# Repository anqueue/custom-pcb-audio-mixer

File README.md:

# Custom PCB Audio Mixer

Deej is an open source project that allows an Arduino to control the volume of applications (https://github.com/omriharel/deej). I wanted to make my own mixer for this, however I don't have a 3d printer. Instead I opted for sandwiching two PCBs to house the electronics and connect the sliders to the Arduino.

The PCBs, Arduino Pro Micros, Poteniometers, soldering iron, bolts, and nuts, costed around $50-60.

I opted for Pro Micros as they have a USB-C connector, which is far more sturdy than the Micro USB on the traditional Arduino Micros.

I first prototyped the board on breadboards and used jumper cables. It worked, and sat on my desk for months while I learned how to create the PCBs and get the manufactured.

I finally finished designing the PCB with KiCad, had the manufactured at JLCPCB, and started putting them together, when I realized that the aluminum base material didn't work with through hole components. The exposed back would short out all of the components.

However, this wasn't a total waste of time and money. I went ahead and sat the components on the PCB and realized there were a few other problems, like the lack of space for the Pro Micro.

I redesigned the board with these considerations and had it manufactured on FR-4 this time. There was still a small issue with the positioning of the Pro Micro, so I soldered on extensions to the poteniometers (the left two sliders in the picture).

Overall, from the very first concept to the final design, it took about 6 months. I of course could have done this in far less time, however I had other priorities and was in no rush to finish it. The concept on the breadboard worked identically to the final design. I use my mixer daily, and it is very useful to control the volume of YouTube or Discord while I am in a game.

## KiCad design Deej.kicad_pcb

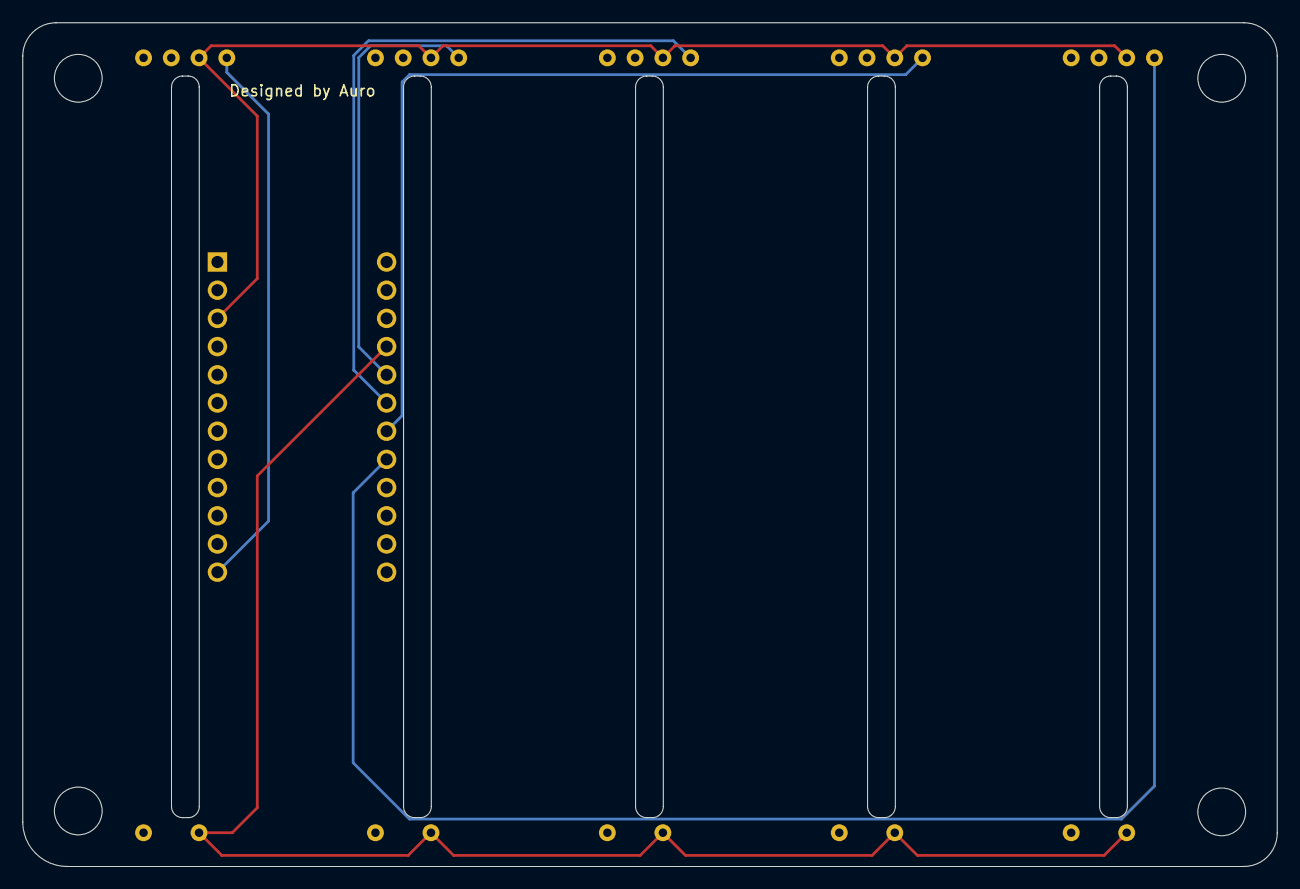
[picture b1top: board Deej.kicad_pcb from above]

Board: 2 copper layers, 113.0 x 76.0 mm, 10 parts (0 on the bottom side), 7 nets.

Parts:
H1, H2, H3, H4: MountingHole; MountingHole_4.3mm_M4_ISO7380
U1: ProMicro; ArduinoProMicro
VR1, VR2, VR3, VR4, VR5: Slider; Fdeej-slider

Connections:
GND: U1.3 (GND), VR1.2, VR2.2, VR3.2, VR4.2, VR5.2
unnamed: U1.12 (9/PB5), VR1.1
unnamed: U1.17 (A0/PF7), VR5.1
unnamed: U1.18 (A1/PF6), VR4.1
unnamed: U1.19 (A2/PF5), VR3.1
unnamed: U1.20 (A3/PF4), VR2.1
unnamed: U1.21 (VCC), VR1.5, VR2.5, VR3.5, VR4.5, VR5.5

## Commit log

2024-10-01 Upload deej schematic files
